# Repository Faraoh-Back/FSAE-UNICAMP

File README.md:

# FSAE-UNICAMP
Este repositório centraliza todos os códigos e desenvolvimentos de software da equipe Fórmula SAE. Aqui você encontrará os firmwares, algoritmos e ferramentas utilizados em nosso protótipo.

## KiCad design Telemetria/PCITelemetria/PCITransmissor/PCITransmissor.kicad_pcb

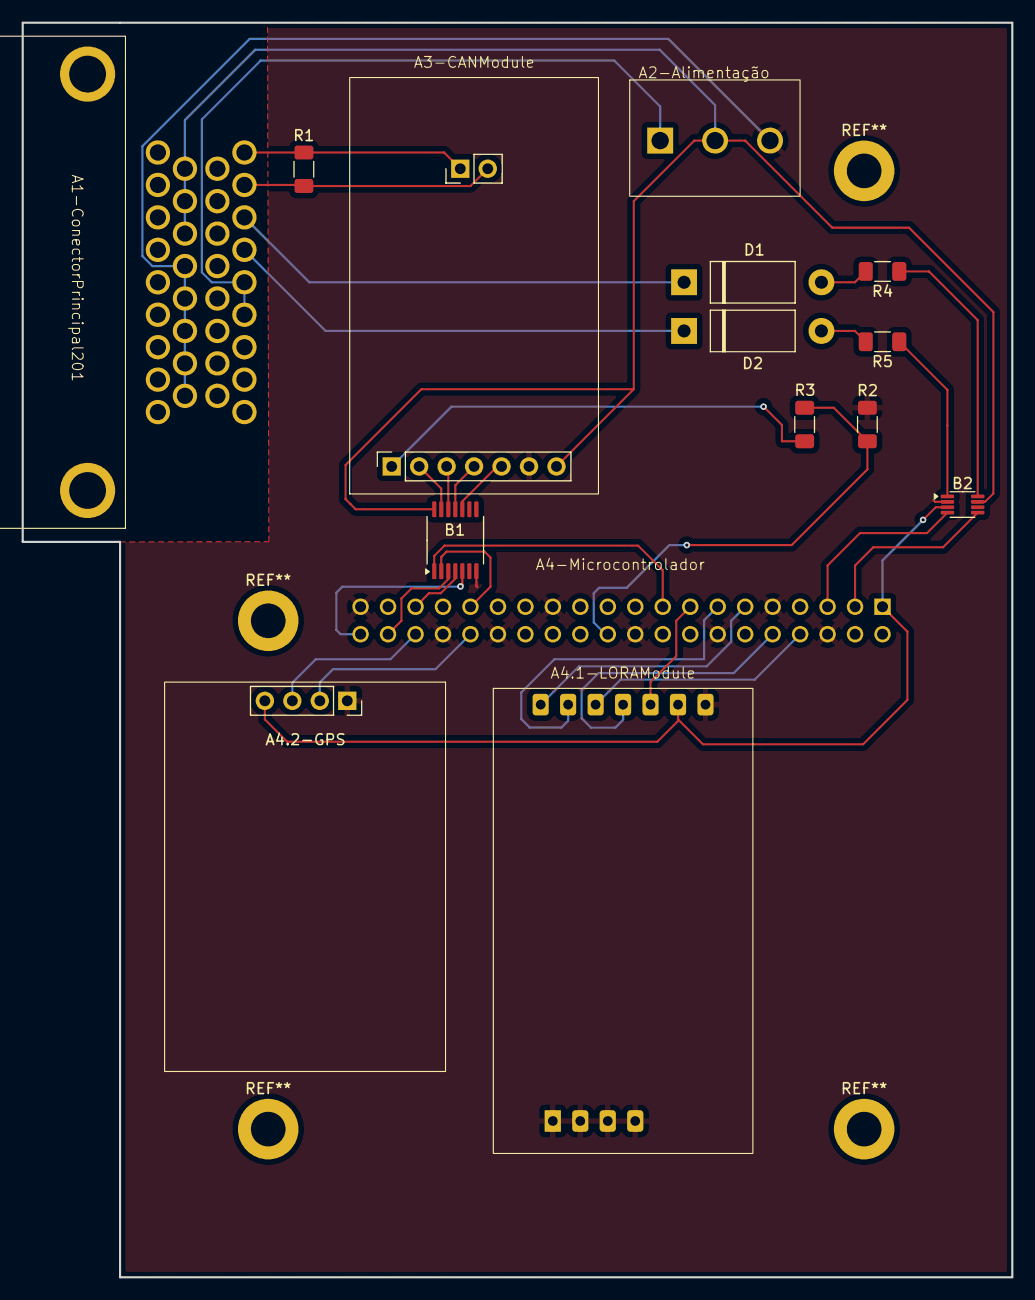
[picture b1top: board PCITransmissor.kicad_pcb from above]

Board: 2 copper layers, 91.5 x 116.0 mm, 15 parts (0 on the bottom side), 31 nets.

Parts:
A1-ConectorPrincipal201: 3-6437285-0; Conector_Principal
A2-Alimentação: TB007-508-03BE; Alimentação_5_12_GND
A3-CANModule: MCP2515
A4-Microcontrolador: RASPBERRY_PI_5; Conector_Raspberry_PI_5
A4.1-LORAModule: E22-900T30D
A4.2-GPS: GY-NEO6MV2; PinSocket_1x04_P2.54mm_Vertical
B1: TXB0104PW; TSSOP-14_4.4x5mm_P0.65mm
B2: TXB0102DCU; VSSOP-8_2.3x2mm_P0.5mm
D1, D2: Diode; P1_DO-15
R1: 120Ω; R_1206_3216Metric_Pad1.30x1.75mm_HandSolder
R2: 2KΩ; R_1206_3216Metric_Pad1.30x1.75mm_HandSolder
R3: 1KΩ; R_1206_3216Metric_Pad1.30x1.75mm_HandSolder
R4, R5: 100Ω; R_1206_3216Metric_Pad1.30x1.75mm_HandSolder

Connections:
/AUX_LORA: A4-Microcontrolador.15 (GPIO22/GPIO_GEN3), A4.1-LORAModule.5 (AUX)
/CS_CAN_A1: A4-Microcontrolador.31 (GPIO6), B1.2 (A1)
/INT_CAN: A4-Microcontrolador.22 (GPIO25/GPIO_GEN6), R2.1, R3.2
/M0_LORA: A4-Microcontrolador.11 (GPIO17/GPIO_GEN0), A4.1-LORAModule.1 (M0)
/M1_LORA: A4-Microcontrolador.13 (GPIO27/GPIO_GEN2), A4.1-LORAModule.2 (M1)
/PCB_ConectorPrincipal/CS_CAN_B1: A3-CANModule.2 (SCK), B1.13 (B1)
/PCB_ConectorPrincipal/SCK_CAN_B4: A3-CANModule.5 (CS), B1.10 (B4)
/PCB_ConectorPrincipal/SCL_Conector_B2: B2.1 (B2), R5.1
/PCB_ConectorPrincipal/SDA_Conector_B1: B2.8 (B1), R4.1
/PCB_ConectorPrincipal/SI_CAN_B2: A3-CANModule.3 (SI), B1.12 (B2)
/PCB_ConectorPrincipal/SO_CAN_B3: A3-CANModule.4 (SO), B1.11 (B3)
/RX_GPS: A4-Microcontrolador.36 (GPIO16), A4.2-GPS.3
/RX_LORA: A4-Microcontrolador.8 (GPIO14/TXD0), A4.1-LORAModule.3 (RXEN)
/SCK_CAN_A4: A4-Microcontrolador.40 (GPIO21), B1.5 (A4)
/SCL_Conector: A4-Microcontrolador.5 (GPIO3/SCL1), B2.4 (A2)
/SDA_Conector: A4-Microcontrolador.3 (GPIO2/SDA1), B2.5 (A1)
/SI_CAN_A2: A4-Microcontrolador.38 (GPIO20), B1.3 (A2)
/SO_CAN_A3: A4-Microcontrolador.35 (GPIO19), B1.4 (A3)
/TX_GPS: A4-Microcontrolador.32 (GPIO12), A4.2-GPS.2
/TX_LORA: A4-Microcontrolador.10 (GPIO15/RXD0), A4.1-LORAModule.4 (TXEN)
GND: A1-ConectorPrincipal201.13 (GND), A1-ConectorPrincipal201.14 (GND), A1-ConectorPrincipal201.15 (GND), A1-ConectorPrincipal201.16 (GND), A1-ConectorPrincipal201.17 (GND), A2-Alimentação.3 (GND), A3-CANModule.6 (GND), A4-Microcontrolador.6 (GND), A4-Microcontrolador.9 (GND), A4-Microcontrolador.14 (GND), A4-Microcontrolador.20 (GND), A4-Microcontrolador.25 (GND), A4-Microcontrolador.30 (GND), A4-Microcontrolador.34 (GND), A4-Microcontrolador.39 (GND), A4.1-LORAModule.7 (GND), A4.1-LORAModule.8 (GND), A4.1-LORAModule.9 (GND), A4.1-LORAModule.10 (GND), A4.1-LORAModule.11 (GND), A4.2-GPS.1, B1.7 (GND), B2.2 (GND), R2.2
unnamed: A1-ConectorPrincipal201.26 (CAN_H), A3-CANModule.8 (CANAL_H), R1.2
unnamed: A1-ConectorPrincipal201.27 (CAN_L), A3-CANModule.9 (CANAL_L), R1.1
unnamed: A1-ConectorPrincipal201.29 (SCL), D2.1 (A)
unnamed: A1-ConectorPrincipal201.28 (SDA), D1.1 (A)
unnamed: A3-CANModule.1 (INT), R3.1
unnamed: D1.2 (C), R4.2
unnamed: D2.2 (C), R5.2
VCC_3V: A4-Microcontrolador.1 (3V3), A4-Microcontrolador.17 (3V3), A4.1-LORAModule.6 (VCC), A4.2-GPS.4, B1.1 (VCCA), B2.3 (VCCA)
VCC_5V: A1-ConectorPrincipal201.10 (VCC), A1-ConectorPrincipal201.11 (VCC), A1-ConectorPrincipal201.12 (VCC), A2-Alimentação.2 (VCC), A3-CANModule.7 (VCC), B1.14 (VCCB), B2.7 (VCCB)
VCC_12V: A1-ConectorPrincipal201.30 (VCC_12V), A1-ConectorPrincipal201.31 (VCC_12V), A2-Alimentação.1 (VCC_12V)

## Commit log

2025-07-03 Primeiro commit
2025-07-09 Inserindo o código para testar o rádio LORA
2025-07-09 Adicionando o código Principal da Telemetria
2025-07-09 Documentação Inicial
2025-07-09 Arrumando
2025-07-10 Adicionando documentação de descriptografia do protocoloca CAN_FT2.0
2025-07-10 Adicionei o firmware de teste e o arquivo .gitignore para que ninguem envie o ambiente virtual
2025-07-11 Adicionando os sensores corretos que serão transmitidos
2025-07-11 Adicionando a pasta nível 2 com alteração
2025-07-11 Adicionando o código de teste da ESP8266
2025-07-11 Adicionando os códigos e instruções para o funcionamento da Raspberry Principal da Telemetria
2025-07-11 Mudei os pinos rx e tx
2025-07-11 Alguma coisa
2025-07-12 Alterações
2025-07-12 Arrumando os firmware de teste da esp8266 e do arduino
2025-07-12 Adicionando o código de Teste da Raspberry testado e aprovado
2025-07-12 Arrumando o código de teste da ESP8266_Base
2025-07-13 Firmware funcional de teste para a ESP8266
2025-07-13 Arrumando a estrutura de pasta
2025-07-13 Arrumando estrutura de pasta
2025-07-14 Arrumando bug do firmware de teste da Raspberry
2025-07-14 Adicionando print para debbugar
2025-07-14 Arrumei o que tinha estragado kkkk
2025-07-14 Arrumando a estrutura de pacotes (TESTE)
2025-07-14 Arrumando teste
2025-07-14 Adicionando melhorias ao codigo e vendo se funciona.
2025-07-14 Adicionando mais debuger
2025-07-14 Mudei de lib para uma mais consistente a E22
2025-07-15 Debbugador fernanda
2025-07-15 Tentando colocar configurações no lora da maneira ugabua
2025-07-18 Adicionando o protocolo Wifi
2025-07-18 Adicionando requirements.txt das balanças
2025-07-19 Adicionando código do SoundGate
2025-07-19 Arrumando algumas coisas do SoundGate
2025-07-20 Adicionando o Ultrasonic.h do SoundGate
2025-07-21 Organizando os protocolos e adicionando o MoT para Wifi
2025-07-21 Arrumando nome de pastas
2025-07-21 Adicionando
2025-07-22 Mudando o Protocolo_Wifi(Principal) para rodar em supabase
2025-07-24 Estruturando em estrutura MVC o protocolo de wifi principal
2025-07-30 Arrumando a ordem dos valores das balanças da imagem
